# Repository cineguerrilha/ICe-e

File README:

Integrated ephys plataform Intan/BB/Arduino

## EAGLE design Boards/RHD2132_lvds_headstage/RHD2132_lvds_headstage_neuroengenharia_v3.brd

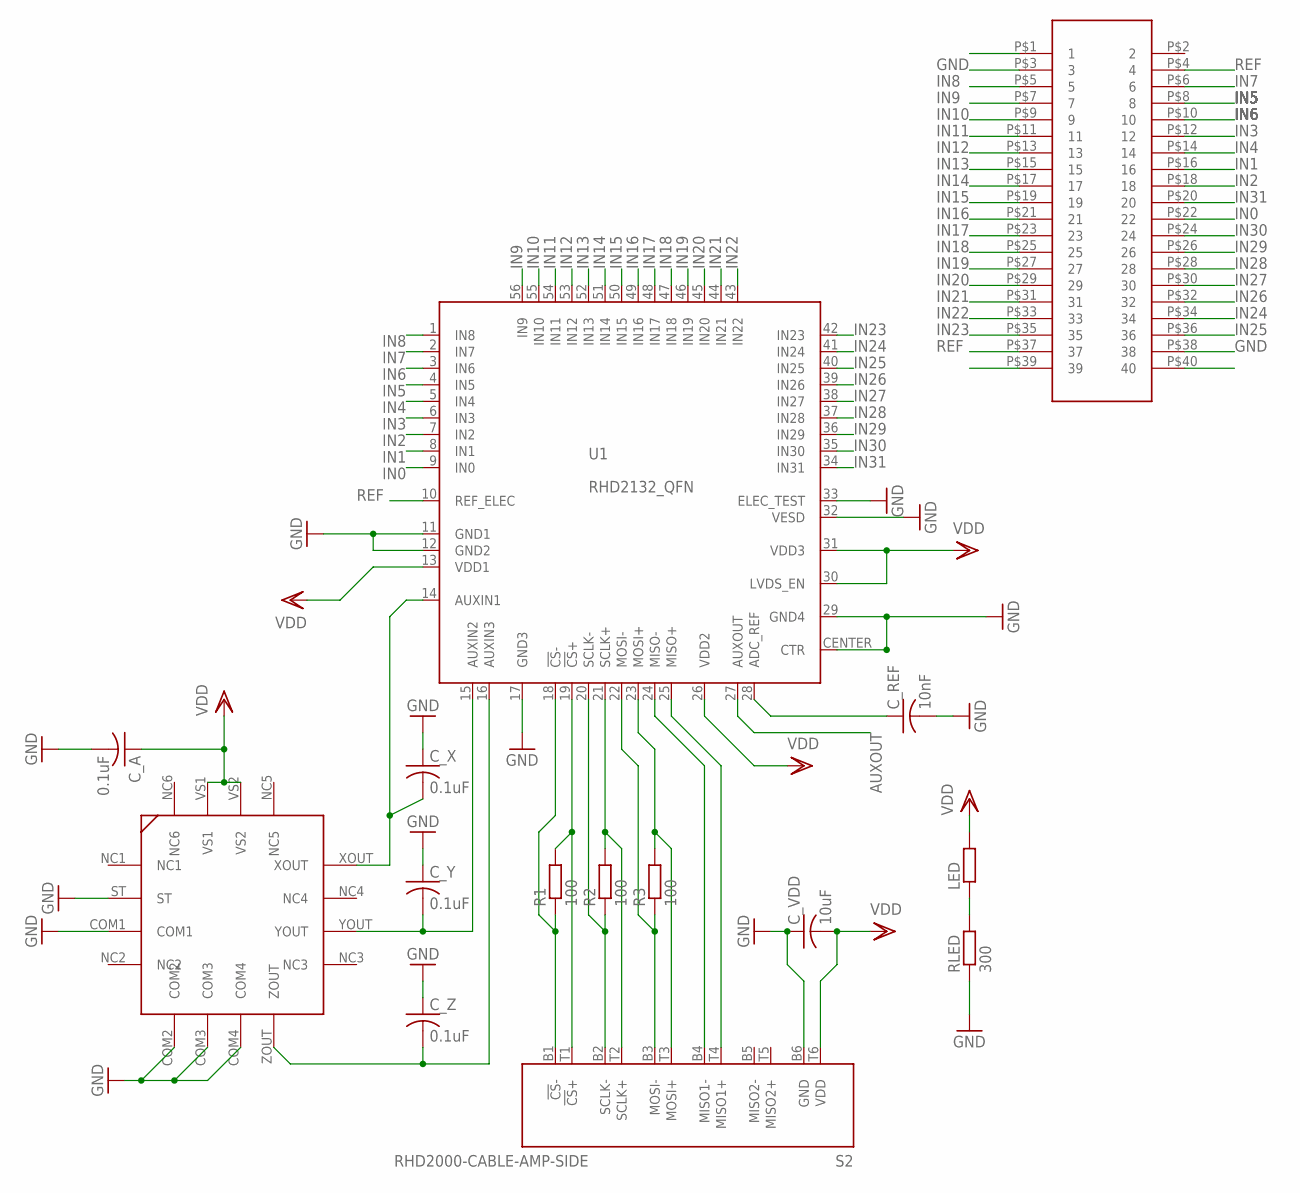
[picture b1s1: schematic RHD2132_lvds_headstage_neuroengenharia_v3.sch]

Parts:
C_A: 0.1uF; C0402K
C_REF: 10nF; C0402K
C_VDD: 10uF; C0402K
C_X: 0.1uF; C0402K
C_Y: 0.1uF; C0402K
C_Z: 0.1uF; C0402K
LED: R-EU_R0402; R0402
R1, R2, R3: 100; R0402
RLED: 300; R0402
S2: RHD2000-CABLE-AMP-SIDE; OMNETICS_PZN-12-AA
U1: RHD2132_QFN; QFN56_8_X_8_LARGE
U$1: ADXL335
U$2: MOLEX_552010478; MOLEX

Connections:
ADC_REF: C_REF.1, U1.28 (ADC_REF)
AUXOUT: U1.27 (AUXOUT)
CS+: R1.2, S2.T1 (!CS!+), U1.19 (!CS!+)
CS-: R1.1, S2.B1 (!CS!-), U1.18 (!CS!-)
GND: C_A.2, C_REF.2, C_VDD.1, C_X.1, C_Y.1, C_Z.1, RLED.1, S2.B6 (GND), U1.11 (GND1), U1.12 (GND2), U1.17 (GND3), U1.29 (GND4), U1.32 (VESD), U1.33 (ELEC_TEST), U1.CENTER (CTR), U$1.COM1, U$1.COM2, U$1.COM3, U$1.COM4, U$1.ST, U$2.P$3 (3), U$2.P$38 (38)
IN0: U1.9 (IN0), U$2.P$22 (22)
IN1: U1.8 (IN1), U$2.P$16 (16)
IN2: U1.7 (IN2), U$2.P$18 (18)
IN3: U1.6 (IN3), U$2.P$12 (12)
IN4: U1.5 (IN4), U$2.P$14 (14)
IN5: U1.4 (IN5), U$2.P$8 (8)
IN6: U1.3 (IN6), U$2.P$10 (10)
IN7: U1.2 (IN7), U$2.P$6 (6)
IN8: U1.1 (IN8), U$2.P$5 (5)
IN9: U1.56 (IN9), U$2.P$7 (7)
IN10: U1.55 (IN10), U$2.P$9 (9)
IN11: U1.54 (IN11), U$2.P$11 (11)
IN12: U1.53 (IN12), U$2.P$13 (13)
IN13: U1.52 (IN13), U$2.P$15 (15)
IN14: U1.51 (IN14), U$2.P$17 (17)
IN15: U1.50 (IN15), U$2.P$19 (19)
IN16: U1.49 (IN16), U$2.P$21 (21)
IN17: U1.48 (IN17), U$2.P$23 (23)
IN18: U1.47 (IN18), U$2.P$25 (25)
IN19: U1.46 (IN19), U$2.P$27 (27)
IN20: U1.45 (IN20), U$2.P$29 (29)
IN21: U1.44 (IN21), U$2.P$31 (31)
IN22: U1.43 (IN22), U$2.P$33 (33)
IN23: U1.42 (IN23), U$2.P$35 (35)
IN24: U1.41 (IN24), U$2.P$34 (34)
IN25: U1.40 (IN25), U$2.P$36 (36)
IN26: U1.39 (IN26), U$2.P$32 (32)
IN27: U1.38 (IN27), U$2.P$30 (30)
IN28: U1.37 (IN28), U$2.P$28 (28)
IN29: U1.36 (IN29), U$2.P$26 (26)
IN30: U1.35 (IN30), U$2.P$24 (24)
IN31: U1.34 (IN31), U$2.P$20 (20)
LEDOUT: LED.1, RLED.2
MISO1+: S2.T4 (MISO1+), U1.25 (MISO+)
MISO1-: S2.B4 (MISO1-), U1.24 (MISO-)
MOSI+: R3.2, S2.T3 (MOSI+), U1.23 (MOSI+)
MOSI-: R3.1, S2.B3 (MOSI-), U1.22 (MOSI-)
REF: U1.10 (REF_ELEC), U$2.P$4 (4), U$2.P$37 (37)
SCLK+: R2.2, S2.T2 (SCLK+), U1.21 (SCLK+)
SCLK-: R2.1, S2.B2 (SCLK-), U1.20 (SCLK-)
VDD: C_A.1, C_VDD.2, LED.2, S2.T6 (VDD), U1.13 (VDD1), U1.26 (VDD2), U1.30 (LVDS_EN), U1.31 (VDD3), U$1.VS1, U$1.VS2
XOUT: C_X.2, U1.14 (AUXIN1), U$1.XOUT
YOUT: C_Y.2, U1.15 (AUXIN2), U$1.YOUT
ZOUT: C_Z.2, U1.16 (AUXIN3), U$1.ZOUT

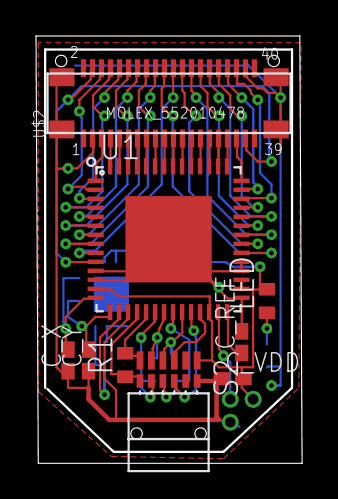
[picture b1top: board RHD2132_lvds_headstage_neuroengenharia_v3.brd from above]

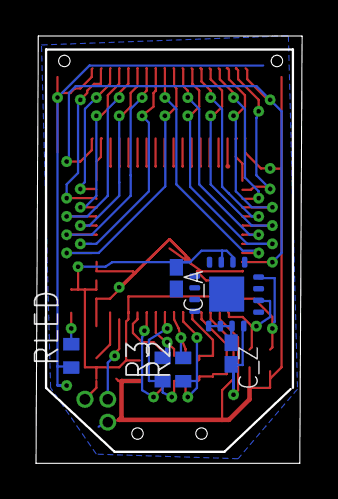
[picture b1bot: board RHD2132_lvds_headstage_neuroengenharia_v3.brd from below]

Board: 2 copper layers, 14.7 x 23.6 mm, 15 parts (6 on the bottom side), 48 nets.

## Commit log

2012-12-02 Trying to add files
2012-12-03 3rd commit
2012-12-04 4th commit
2012-12-04 Final commitment for data acquisition, RL
2012-12-04 Final commit + fdd drivers
2012-12-04 Final commit updated
2012-12-10 Added the intan original software
2015-11-19 Intan for VS2012
    New intan prog for vs2012
2018-03-22 New VS2013 software
    New VS2013 software and arduino progs
2018-06-07 New miniscope control software
    few improvements
2018-06-21 Little program to run the treadmill using the NI6009
    VS2013 program to run the treadmill modifying the analog output of the NI.
2019-05-15 Create CV_test.py
    Miniscope acquisition in python
2019-05-21 Miniscope acquisition
    Started coding the miniscope python acquisition program
2019-05-29 behavior cam control rasp pi
2019-06-03 More on behaviour
2019-06-20 PupilMeasurment
2019-06-21 POMidaq miniscope prog compiled
2019-06-26 Behavior detections for optogenetics
    It might work on the pi
2019-07-24 behavior py cam
2019-08-30 Create BehaviourCam.py
    Python routine to trigger acquisition when a pulse
